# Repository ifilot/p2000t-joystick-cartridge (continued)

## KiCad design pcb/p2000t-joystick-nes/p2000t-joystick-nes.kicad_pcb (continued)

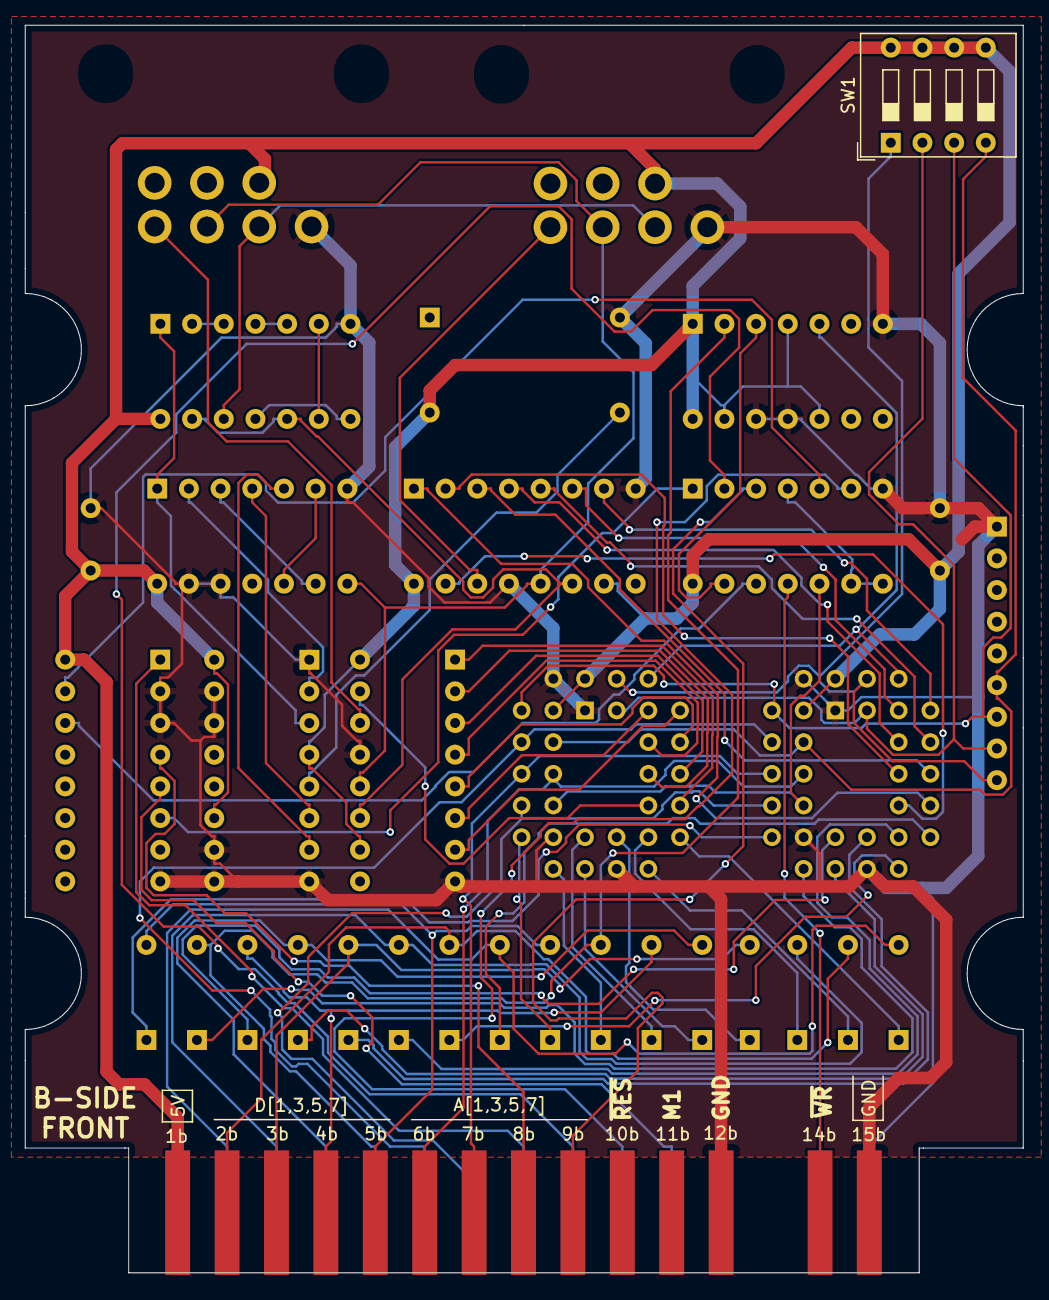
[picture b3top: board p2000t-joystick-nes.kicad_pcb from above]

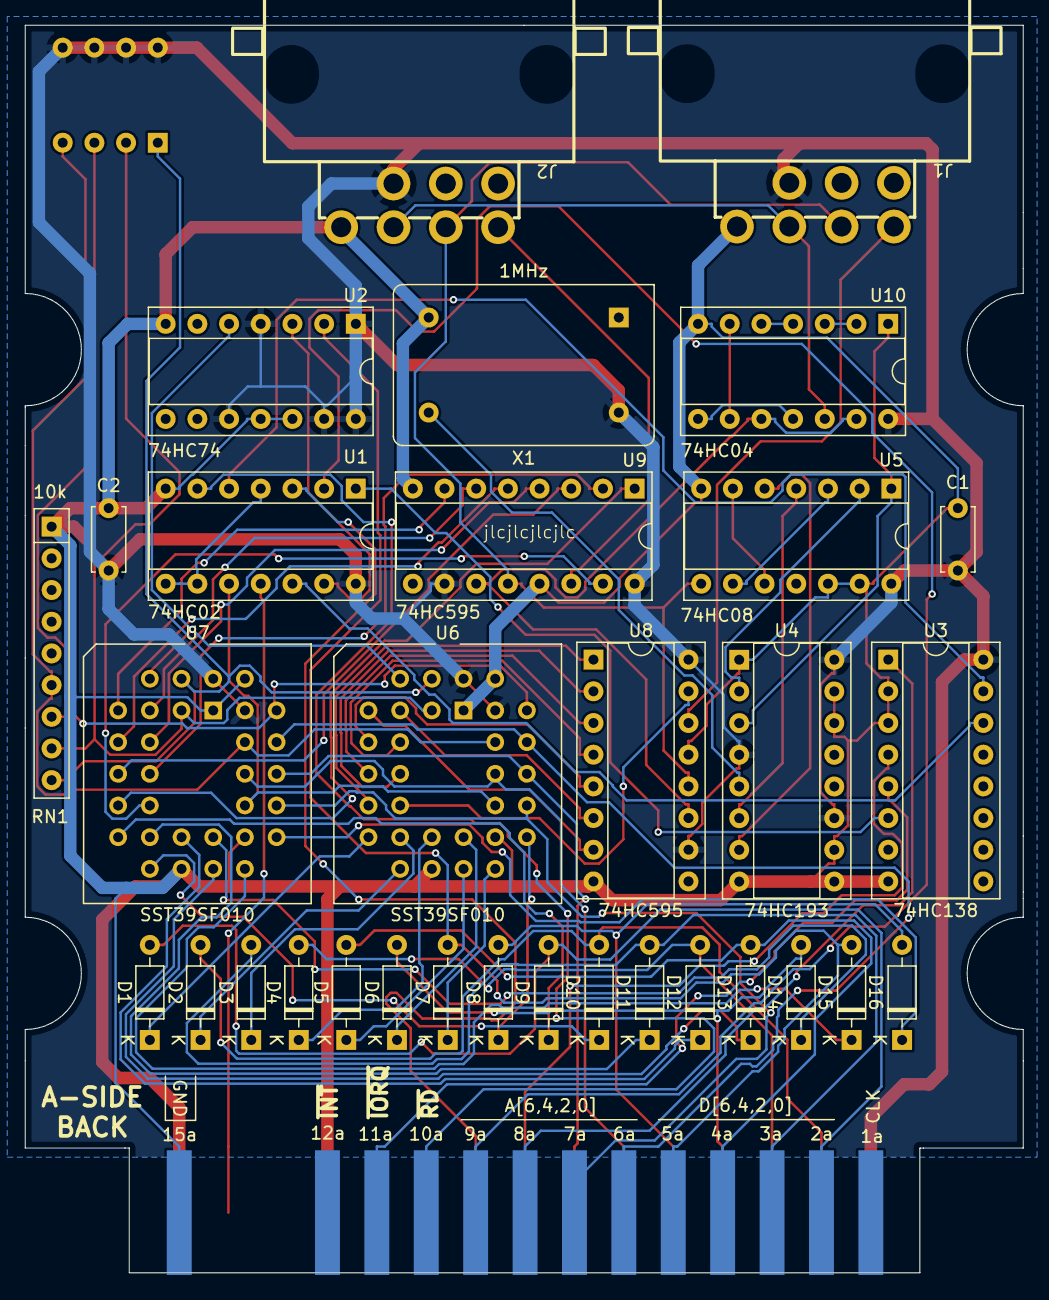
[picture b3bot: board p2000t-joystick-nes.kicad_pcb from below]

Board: 2 copper layers, 80.0 x 100.0 mm, 34 parts (33 on the bottom side), 80 nets.

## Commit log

2025-01-23 Refining README.md
2025-01-23 Expanding README.md
2025-01-23 Revising joystick case
2025-01-23 Revising cases
2025-01-23 Rev1
2025-01-24 Revising case
2025-01-24 Expanding mappings
2025-01-28 Initial commit cartridge for NES controller
2025-01-28 Refining layout
2025-01-28 Adding nightly build
2025-01-28 Adding dependency
2025-01-28 Fixing filename
2025-01-28 Modifying README.md
2025-01-29 Pre-routing commit
2025-01-30 Routing
2025-02-08 Adding script
2025-04-05 Initial commit CPLD variant
2025-04-05 Initial commit CPLD script
2025-04-17 Tuning CPLD
2025-04-21 Fixing design and CUPL
